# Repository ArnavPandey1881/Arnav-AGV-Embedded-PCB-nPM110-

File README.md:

# Arnav-AGV-Embedded-PCB-nPM110-
AIM:
This project involves the design of a 4-layer PCB using KiCad for the nPM1100 Power Management IC.The schematic is created based on the reference configuration provided in the datasheet, and the PCB layout is developed with proper component placement, grounding, and routing techniques.

FEATURES OF MODEL:
Battery charging and power management
4-layer PCB design
Ground plane implementation

SOFTWARE USED:
KiCad EDA

FILES INCLUDED:
Npm1100.kicad_sch → Schematic
Npm1100.kicad_pcb → PCB Layout
Npm1100.pdf → Schematic PDF
pcb.pdf → PCB PDF

SOME APPROACHES:
Followed datasheet reference design given.
Used In1.Cu as GND plane and In2.Cu as power plane to connect VBUS,VSYS and VBAT.
Routed power signals (VBUS, VBAT, VSYS) using tracks in In2.Cu.
Added vias to connect GND pads to ground plane.
Tried to place capacitors and inductor near the centre.
Used PCB calculator to get trace width.
Added LED to ERR and CHG to get indications.
Added connector 1x2 header pin to get input.

AUTHOR:
Arnav Pandey

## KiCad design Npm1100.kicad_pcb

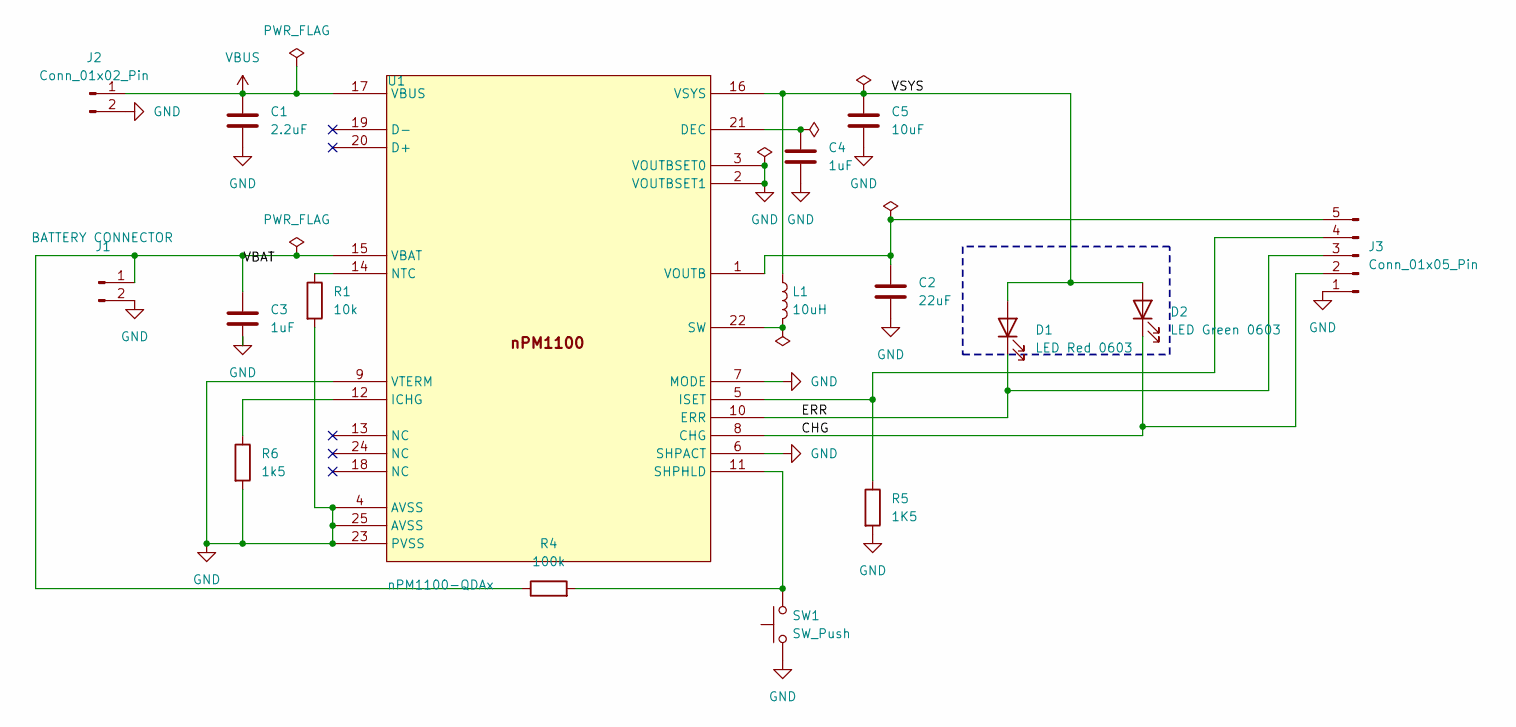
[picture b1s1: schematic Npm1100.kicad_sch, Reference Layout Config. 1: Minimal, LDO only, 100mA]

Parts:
C1: 2.2uF; C_0603_1608Metric
C2: 22uF; C_0603_1608Metric
C3, C4: 1uF; C_0603_1608Metric
C5: 10uF; C_0603_1608Metric_Pad1.08x0.95mm_HandSolder
D1: LED Red 0603; LED_0603_1608Metric
D2: LED Green 0603; LED_0603_1608Metric
J1: BATTERY CONNECTOR; JST_PH_B2B-PH-SM4-TB_1x02-1MP_P2.00mm_Vertical
J2: Conn_01x02_Pin; PinHeader_1x02_P2.54mm_Vertical_SMD_Pin1Left
J3: Conn_01x05_Pin; PinHeader_1x05_P2.54mm_Vertical_SMD_Pin1Left
L1: 10uH; L_1210_3225Metric
R1: 10k; R_0603_1608Metric
R4: 100k; R_0603_1608Metric
R5: 1K5; R_0603_1608Metric
R6: 1k5; R_0603_1608Metric
SW1: SW_Push; SW_Push_1P1T_NO_CK_KMR2
U1: nPM1100-QDAx; QFN-24-1EP_4x4mm_P0.5mm_EP2.5x2.5mm

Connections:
/CHG: D2.1 (K), J3.2, U1.8 (CHG)
/ERR: D1.1 (K), J3.3, U1.10 (ERR)
/VBAT: C3.1, J1.1, R4.1, U1.15 (VBAT)
/VSYS: C5.1, D1.2 (A), D2.2 (A), L1.1, U1.16 (VSYS)
GND: C1.2, C2.2, C3.2, C4.2, C5.2, J1.2, J2.2, J3.1, R1.2, R5.2, R6.2, SW1.1, U1.2 (VOUTBSET1), U1.3 (VOUTBSET0), U1.4 (AVSS), U1.6 (SHPACT), U1.7 (MODE), U1.9 (VTERM), U1.23 (PVSS), U1.25 (AVSS)
unnamed: J3.4, R5.1, U1.5 (ISET)
unnamed: C2.1, J3.5, U1.1 (VOUTB)
unnamed: C4.1, U1.21 (DEC)
unnamed: R6.1, U1.12 (ICHG)
unnamed: R1.1, U1.14 (NTC)
unnamed: R4.2, SW1.2, U1.11 (SHPHLD)
unnamed: L1.2, U1.22 (SW)
VBUS: C1.1, J2.1, U1.17 (VBUS)

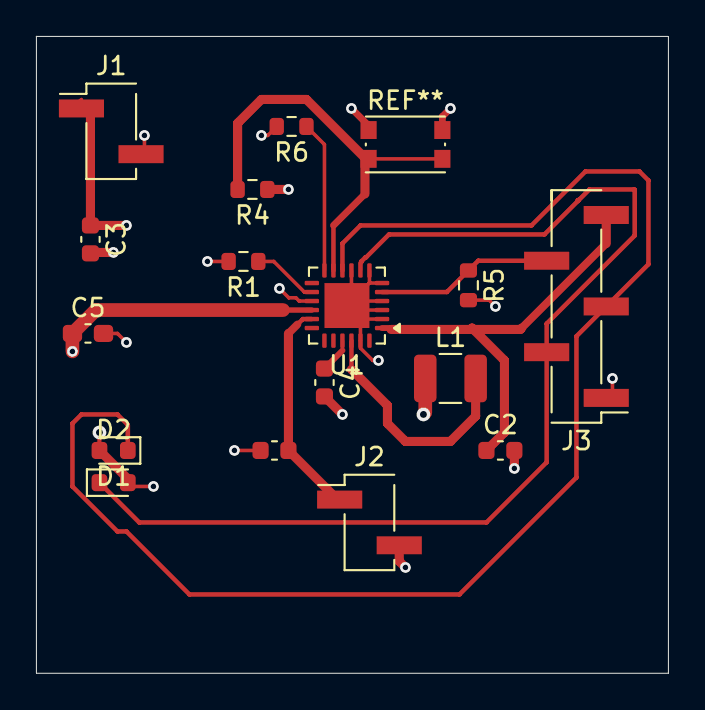
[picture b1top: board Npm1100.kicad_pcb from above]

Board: 4 copper layers, 35.1 x 35.4 mm, 16 parts (0 on the bottom side), 13 nets.

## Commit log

2026-03-30 Create task
2026-03-30 README.md
